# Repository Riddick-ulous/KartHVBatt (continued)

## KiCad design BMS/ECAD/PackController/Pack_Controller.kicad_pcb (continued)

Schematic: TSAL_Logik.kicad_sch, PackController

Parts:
C1001, C1002: 1uF 100V; C_0805_2012Metric
C1003, C1004, C1005, C1006, C1007, C1008: 100nC 16V; C_0603_1608Metric
D1001, D1002, D1003: BAT46; D_SOD-123
Q1001: FDN352AP; SOT-23
Q1002: BC846; SOT-23
R1001, R1002, R1003: 10kR 0603; R_0603_1608Metric_Pad0.98x0.95mm_HandSolder
R1004, R1005: 100kR; R_0603_1608Metric
R1006: 1kR; R_0603_1608Metric
U1001: SN74LVC2G02; VSSOP-8_2.3x2mm_P0.5mm
U1002: 74LVC86AD; SO-14_3.9x8.65mm_P1.27mm
U1003: 74LV08; SO-14_3.9x8.65mm_P1.27mm
U1004: 74LVC1G32Q; SOT-353_SC-70-5
U1005: SN74LVC1G74; VSSOP-8_2.3x2mm_P0.5mm
U1006: CD4072BPW; TSSOP-14_4.4x5mm_P0.65mm
U1007: SN74LVC2G17DCK; SOT-23-6
U1008: SN74LVC2G14DBV; SOT-23-6

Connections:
+3.3V: C1003.1, C1004.1, C1005.1, C1006.1, C1007.1, C1008.1, D1001.1 (K), R1005.2, U1001.8 (VCC), U1002.14 (VCC), U1003.14 (VCC), U1004.5 (VCC), U1005.4 (GND), U1006.14 (VDD), U1007.5 (V_{CC}), U1008.5 (V_{CC}); also elsewhere on the board
+BATT: Q1001.2 (S), R1001.2; also elsewhere on the board
/AIR/AIR_N_Actual: U1002.5, U1003.2, U1006.10; also elsewhere on the board
/AIR/AIR_N_Intended: U1002.4, U1002.9; also elsewhere on the board
/AIR/AIR_P_Actual: U1002.2, U1006.9; also elsewhere on the board
/AIR/AIR_P_Intended: U1002.1; also elsewhere on the board
/AIR/nAIR_Error: U1008.1 (1A); also elsewhere on the board
/HV_Measurement/nDANGER_V: U1003.1, U1008.3 (2A); also elsewhere on the board
/MCU/PCHRG_ACTUAL: U1002.10, U1004.2, U1006.11; also elsewhere on the board
/MCU/TSAL_GRN_ON: R1003.2, U1003.8; also elsewhere on the board
/Precharge/PCHRG_Intended: U1004.1; also elsewhere on the board
/TSAL_GRN: D1003.1 (K); also elsewhere on the board
/TSAL_Logik/AIR_Error: U1001.2, U1008.6 (1Y)
/TSAL_Logik/DANGER_V: U1006.12, U1008.4 (2Y)
/TSAL_Logik/TS_ON: U1001.6, U1006.13
GND: C1001.2, C1002.2, C1003.2, C1004.2, C1005.2, C1006.2, C1007.2, C1008.2, Q1002.2 (E), U1001.4 (GND), U1002.7 (GND), U1002.12, U1002.13, U1003.7 (GND), U1003.12, U1003.13, U1004.3 (GND), U1005.1 (CLK), U1005.2 (D), U1005.8 (VCC), U1006.7 (VSS), U1007.2 (GND), U1008.2 (GND); also elsewhere on the board
unnamed: C1002.1, D1001.2 (A), R1005.1, U1007.3 (2A)
unnamed: D1002.2 (A), R1004.1, U1001.7
unnamed: D1002.1 (K), R1006.1
unnamed: D1003.2 (A), Q1001.3 (D)
unnamed: Q1001.1 (G), R1002.2
unnamed: Q1002.1 (B), R1003.1
unnamed: Q1002.3 (C), R1001.1, R1002.1
unnamed: U1001.1, U1006.1
unnamed: U1001.3, U1003.9
unnamed: U1002.3, U1006.2
unnamed: U1002.6, U1006.3
unnamed: U1002.8, U1006.4
unnamed: U1003.3, U1003.4
unnamed: U1003.5, U1004.4
unnamed: U1003.6, U1006.5
unnamed: U1001.5, U1005.5 (Q)
unnamed: U1003.10, U1005.6 (nCLR), U1007.4 (2Y)
unnamed: U1005.7 (nPRE), U1007.6 (1Y)
unnamed: C1001.1, R1004.2, R1006.2, U1007.1 (1A)

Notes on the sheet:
RC filter delays error detection to filter out AIR operate-/release-times and other timing discrepancies that arise from hardware design.
ERROR = !(AIR_P_ACT == AIR_P_INT) or !(AIR_N_ACT == AIR_N_INT) or !(PCHRG_ACT == AIR_N_INT) or (!DANGER_V and AIR_N_ACT and (PCHRG_ACT or AIR_P_ACT)) or AIR_ERROR TS_ON = AIR_P_ACT or AIR_N_ACT or PCHRG_ACT or DANGER_V GREEN = !(TS_ON or ERROR_LATCH)
POR: Capacitor charges from 0V to 3.3V when power supply is applied. This triggers the clear function of the flip-flop. POR keeps nCLR active for approximately 50...95 ms nominal. Actual delay depends on Schmitt threshold and RC tolerances. GRN_ON-signal also ANDed with POR to only display green af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
base/gate-resistors: 12V/10kOhm 1.2mA 3.3V/10kOhm 0.33mA pullup: reset against eventual leakage of the NPN

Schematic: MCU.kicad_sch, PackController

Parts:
C201, C202, C203, C204, C206, C209, C210, C213, C214: 100nF 0603 6.3V; C_0603_1608Metric_Pad1.08x0.95mm_HandSolder
C205: 6 * 100nF 0603 6.3V; C_0603_1608Metric_Pad1.08x0.95mm_HandSolder
C207: 4.7uF 0805 6.3V; C_0805_2012Metric_Pad1.18x1.45mm_HandSolder
C208: 100nF 0603 16V; C_0603_1608Metric_Pad1.08x0.95mm_HandSolder
C211: 12pF 0603 6.3V; C_0603_1608Metric_Pad1.08x0.95mm_HandSolder
C212: 2 * 12pF 0603 6.3V; C_0603_1608Metric_Pad1.08x0.95mm_HandSolder
D201, D203, D204, D205, D206, D207, D209: BAT46; D_SOD-123
D202: Z 3.3V; D_SOD-323_HandSoldering; PartNr. MM3Z3V3T1G
Error201: LED Red; LED_0805_2012Metric_Pad1.15x1.40mm_HandSolder
Heart201: LED Blue; LED_0805_2012Metric_Pad1.15x1.40mm_HandSolder
JTAG201: JTAG/SWD; PinHeader_2x07_P1.27mm_Vertical
Q201: DMP4065S-7; SOT-23-3
Q202: BC846; SOT-23
R201, R215, R217, R218, R219: 10kR 0603; R_0603_1608Metric_Pad0.98x0.95mm_HandSolder
R202: 2.2k 0603; R_0603_1608Metric_Pad0.98x0.95mm_HandSolder
R203, R205, R206, R207, R208, R211, R213: 10kR; R_0603_1608Metric_Pad0.98x0.95mm_HandSolder
R204, R210, R212: 100R 0603; R_0603_1608Metric_Pad0.98x0.95mm_HandSolder
R209, R216: 20R 0603; R_0603_1608Metric_Pad0.98x0.95mm_HandSolder
R214: 220kR; R_0603_1608Metric_Pad0.98x0.95mm_HandSolder
U201: MCP130-270 ITT; SOT-23
U202: STWD100YNYWY; SOT-23-5
U203: SN74LVC1G74; VSSOP-8_2.3x2mm_P0.5mm
U204: STM32G483VET6; LQFP-100_14x14mm_P0.5mm
U205: 24LC256-I/SN; SOIC-8_5.3x5.3mm_P1.27mm
Y201: WE830055951; Oscillator_SMD_EuroQuartz_XO32-4Pin_3.2x2.5mm

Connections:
+3.3V: C201.1, C202.1, C203.1, C204.1, C205.1, C206.1, C207.1, C208.2, C209.2, C213.2, C214.2, JTAG201.3, R203.1, R206.1, R213.2, R217.2, R218.2, R219.2, U201.2 (VDD), U202.1 (VCC), U203.8 (VCC), U204.6 (VBAT), U204.24 (VDD), U204.36 (VREF+), U204.37 (VDDA), U204.49 (VDD), U204.64 (VDD), U204.75 (VDD), U204.100 (VDD), U205.8 (VCC); also elsewhere on the board
+BATT: R201.2; also elsewhere on the board
/AIR/AIR_N_Actual: U204.93 (PB6); also elsewhere on the board
/AIR/AIR_N_Intended: U204.92 (PB5); also elsewhere on the board
/AIR/AIR_N_Switch: U204.86 (PD4); also elsewhere on the board
/AIR/AIR_P_Actual: U204.89 (PD7); also elsewhere on the board
/AIR/AIR_P_Intended: U204.88 (PD6); also elsewhere on the board
/AIR/AIR_P_Switch: U204.85 (PD3); also elsewhere on the board
/AIR/SC_END: Q201.1 (D); also elsewhere on the board
/AIR/nAIR_Error: U204.94 (PB7); also elsewhere on the board
/Buzzer/Buzzer_CTRL: U204.27 (PA5); also elsewhere on the board
/CAN1/CAN_RX: R209.2; also elsewhere on the board
/CAN1/CAN_TX: U204.73 (PA12); also elsewhere on the board
/CAN2/CAN_RX: R216.2; also elsewhere on the board
/CAN2/CAN_TX: U204.52 (PB13); also elsewhere on the board
/DCDC_AIR/DCDC_AIR_ACTUAL: U204.16 (PC1); also elsewhere on the board
/DCDC_AIR/DCDC_AIR_SWITCH: U204.15 (PC0); also elsewhere on the board
/HV_Measurement/V_ACCU: U204.40 (PE9); also elsewhere on the board
/HV_Measurement/V_VEHI: U204.22 (PA2); also elsewhere on the board
/HV_Measurement/nDANGER_V: U204.26 (PA4); also elsewhere on the board
/HV_Measurement/nPRCHG_DONE: U204.83 (PD1); also elsewhere on the board
/HV_Measurement_DCDC/V_DCDC: U204.44 (PE13); also elsewhere on the board
/HumiditySensing/R_Leak_Sig1: U204.20 (PA0); also elsewhere on the board
/HumiditySensing/R_Leak_Sig2: U204.21 (PA1); also elsewhere on the board
/HumiditySensing/R_Leak_Supply1: U204.19 (PF2); also elsewhere on the board
/HumiditySensing/R_Leak_Supply2: U204.18 (PC3); also elsewhere on the board
/IMD_Monitoring/IMD_OK: U204.41 (PE10); also elsewhere on the board
/IMD_Monitoring/IMD_SC_Closed: U204.43 (PE12); also elsewhere on the board
/IMD_Monitoring/IMD_State: U204.42 (PE11); also elsewhere on the board
/IMD_Monitoring/SC_Out: Q201.3 (S), R205.1; also elsewhere on the board
/MCU/Boot0: R215.1, U204.95 (PB8)
/MCU/ERRQ: U204.61 (PD14); also elsewhere on the board
/MCU/ERRQ_Ioc_out: U204.57 (PD10); also elsewhere on the board
/MCU/ERRQ_ext: U204.59 (PD12); also elsewhere on the board
/MCU/ERRQ_ext_out: U204.58 (PD11); also elsewhere on the board
/MCU/ERRQ_res: U204.60 (PD13); also elsewhere on the board
/MCU/Error: Error201.2 (A), U204.3 (PE4)
/MCU/FAN_PWM: U204.2 (PE3); also elsewhere on the board
/MCU/Heart: Heart201.2 (A), U204.1 (PE2)
/MCU/NTC1_Sig: U204.28 (PA6); also elsewhere on the board
/MCU/NTC2_Sig: U204.39 (PE8); also elsewhere on the board
/MCU/NTC3_Sig: U204.45 (PE14); also elsewhere on the board
/MCU/NTC4_Sig: U204.53 (PB14); also elsewhere on the board
/MCU/NTC5_Sig: U204.30 (PC4); also elsewhere on the board
/MCU/PCHRG_ACTUAL: U204.84 (PD2); also elsewhere on the board
/MCU/PCHRG_SWITCH: U204.82 (PD0); also elsewhere on the board
/MCU/SCL1: R218.1, U204.70 (PA9), U205.6 (SCL)
/MCU/SDA1: R217.1, U204.69 (PA8), U205.5 (SDA)
/MCU/TSAL_GRN_ON: U204.9 (PC15); also elsewhere on the board
/MCU/UART_HS_RX: U204.31 (PC5); also elsewhere on the board
/MCU/UART_HS_TX: U204.97 (PE0); also elsewhere on the board
/MCU/UART_LS_RX: U204.25 (PA3); also elsewhere on the board
/MCU/UART_LS_TX: U204.87 (PD5); also elsewhere on the board
/MCU/WD_Beat: U202.4 (WDI), U204.98 (PE1)
/MCU/WP1: R219.1, U204.29 (PA7), U205.7 (WP)
/MCU/nSleep: U204.62 (PD15); also elsewhere on the board
Batt_Meas: C210.1, D202.1 (K), R201.1, R202.2, U204.33 (PB1)
GND: C201.2, C202.2, C203.2, C204.2, C205.2, C206.2, C207.2, C209.1, C210.2, C211.1, C212.1, C213.1, C214.1, JTAG201.5, JTAG201.7, JTAG201.11, Q202.2 (E), R202.1, R204.2, R210.2, R211.1, R212.1, R214.2, R215.2, U201.3 (VSS), U202.3 (!EN), U203.1 (CLK), U203.2 (D), U203.4 (GND), U204.23 (VSS), U204.35 (VSSA), U204.48 (VSS), U204.63 (VSS), U204.74 (VSS), U204.99 (VSS), U205.1 (A0), U205.2 (A1), U205.3 (A2), U205.4 (GND); also elsewhere on the board
JCLK/SWCLK: JTAG201.6, U204.77 (PA14)
JTDI/NC: JTAG201.10
JTDO/SWO: JTAG201.8, U204.90 (PB3)
JTMS/SWDIO: JTAG201.4, U204.76 (PA13)
Latch_SC: D205.1 (K), U204.65 (PC6)
unnamed: D202.2 (A), R204.1
unnamed: D205.2 (A), D206.2 (A), D207.2 (A), R213.1, U203.6 (nCLR)
unnamed: D209.2 (A), R208.2, U203.5 (Q)
unnamed: Error201.1 (K), R212.2
unnamed: Heart201.1 (K), R210.1
unnamed: Q201.2 (G), R205.2, R207.1
unnamed: Q202.1 (B), R208.1
unnamed: Q202.3 (C), R207.2
unnamed: C208.1, U202.2 (GND)
unnamed: R209.1, U204.72 (PA11)
unnamed: R216.1, U204.51 (PB12)
unnamed: C211.2, U204.12 (PF0), Y201.2
unnamed: C212.2, U204.13 (PF1), Y201.1
SC_Latched: D207.1 (K), R214.1, U204.67 (PC8)
SC_State: D209.1 (K), R211.2
T_VCP_RX: JTAG201.13
T_VCP_TX: JTAG201.14
nPOR: D201.1 (K), D204.1 (K), U201.1 (~RST), U203.7 (nPRE)
nPOR_State: D204.2 (A), R206.2, U204.66 (PC7)
nRES: D201.2 (A), D203.2 (A), JTAG201.12, R203.2, U204.14 (PG10), U204.91 (PB4)
nWDO: D203.1 (K), D206.1 (K), U202.5 (!WDO)

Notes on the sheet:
VBatt = 12V
Place close to VREF GND
SC latch / reset / watchdog logic: U201 MCP130 generates nPOR from +3.3V. nPOR is used only as power-on/brownout set signal for U203A. Power-up / brownout: nPOR = LOW -> U203A nPRE = LOW -> Q = HIGH -> Q202/Q201 enable SC_Out -> D201 also pulls nRES LOW and keeps MCU in reset After nPOR release: nP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

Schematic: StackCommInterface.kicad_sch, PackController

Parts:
C301, C302, C303: 100nF 16V; C_1206_3216Metric
C304: 330nF 50V; C_0805_2012Metric
C305, C306, C307, C308, C310, C311, C312: 2.2nC 100V; C_0603_1608Metric
C309: 2.2nC 1000V; C_0603_1608Metric
C313, C314, C315, C316: 220pC 100V; C_0603_1608Metric
R301: 5.1R; R_0603_1608Metric
R302, R303, R308, R309: 39R; R_0603_1608Metric
R304, R305, R306, R307, R312, R313: 1kR; R_0603_1608Metric
R310: 10kR; R_0603_1608Metric
R311: 1.5kR; R_0603_1608Metric
T301, T302: HM2106NL; Pulse_HM2106NL
U301: TLE9015 DQU; TQFP-48-1EP_7x7mm_P0.5mm_EP5x5mm

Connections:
+3.3V: C303.1, U301.30 (VIO); also elsewhere on the board
+BATT: R301.2; also elsewhere on the board
/MCU/ERRQ: R310.1, U301.33 (ERRQ); also elsewhere on the board
/MCU/ERRQ_Ioc_out: U301.21 (ERRQ_Ioc_out); also elsewhere on the board
/MCU/ERRQ_ext: U301.18 (ERRQ_ext); also elsewhere on the board
/MCU/ERRQ_ext_out: R311.2, U301.20 (ERRQ_ext_out); also elsewhere on the board
/MCU/ERRQ_res: U301.16 (ERRQ_res); also elsewhere on the board
/MCU/UART_HS_RX: R313.2, U301.29 (UART_HS); also elsewhere on the board
/MCU/UART_HS_TX: R313.1; also elsewhere on the board
/MCU/UART_LS_RX: R312.2, U301.28 (UART_LS); also elsewhere on the board
/MCU/UART_LS_TX: R312.1; also elsewhere on the board
/MCU/nSleep: U301.14 (nSleep); also elsewhere on the board
/StackCommInterface/IFH_H: R304.2, T301.1; also elsewhere on the board
/StackCommInterface/IFH_L: R304.1, T301.3; also elsewhere on the board
/StackCommInterface/IFL_H: R307.2, T302.1; also elsewhere on the board
/StackCommInterface/IFL_L: R307.1, T302.3; also elsewhere on the board
/StackCommInterface/VDDC: C304.1, R310.2, R311.1, U301.27 (VDDC)
GND: C301.2, C302.2, C303.2, C304.2, C313.2, C314.2, C315.2, C316.2, U301.22 (GND), U301.49 (EP); also elsewhere on the board
unnamed: C301.1, R301.1, U301.34 (VS), U301.35 (VS)
unnamed: C305.1, C306.2
unnamed: C305.2, R305.2, T301.6
unnamed: C306.1, C313.1, R302.1
unnamed: C307.1, C316.1, R303.1
unnamed: C307.2, C308.1
unnamed: C308.2, R306.2, T302.6
unnamed: C309.1, C310.2
unnamed: C309.2, R305.1, T301.4
unnamed: C310.1, C314.1, R308.1
unnamed: C311.1, C315.1, R309.1
unnamed: C311.2, C312.1
unnamed: C312.2, R306.1, T302.4
unnamed: R302.2, U301.25 (IFH_H)
unnamed: R308.2, U301.26 (IFH_L)
unnamed: R303.2, U301.24 (IFL_H)
unnamed: R309.2, U301.23 (IFL_L)
unnamed: C302.1, U301.31 (VregOut_VDDA)

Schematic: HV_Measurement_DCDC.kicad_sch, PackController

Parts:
C2002, C2006: 100nC 0603 50V; C_0603_1608Metric
C2003, C2015: 100nF 0603 100V; C_0603_1608Metric_Pad1.08x0.95mm_HandSolder
C2004: 100pC 0603 50V; C_0603_1608Metric
C2005, C2007: 10uF 0805 35V; C_0805_2012Metric
C2008: 100nC 0603 16V; C_0603_1608Metric
C2010: 1uC 0805 50V; C_0805_2012Metric
C2012: 1uC 0805 16V; C_0805_2012Metric
C2014: 1nC 0603 16V; C_0603_1608Metric
C2016: 1uF 0805 50V; C_0805_2012Metric
R2001: 270R 0805; R_0805_2012Metric_Pad1.20x1.40mm_HandSolder
R2004, R2005: 4.7MR 2512 3kV 0,1%; R_2512_6332Metric_Pad1.40x3.35mm_HandSolder
R2006: 26.1kR 2512 500V 0,1%; R_2512_6332Metric_Pad1.40x3.35mm_HandSolder
R2008: 1kR; R_0603_1608Metric_Pad0.98x0.95mm_HandSolder
U2002: TEA1-0505HI; Converter_DCDC_TRACO_TEA1-xxxxHI_THT
U2003: AMC0311R; AMC0311R Wide-body SOIC (DWV)
U2004: LP5907MFX-3.3; SOT-23-5

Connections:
+3.3V: C2006.1, U2003.6 (REFIN); also elsewhere on the board
+3.3V_DCDC: C2002.1, C2010.1, C2015.2, C2016.1, U2003.1 (VDD1), U2004.5 (OUT)
+5V: C2007.1, C2008.1, C2012.1, U2002.1 (+Vin), U2003.8 (VDD2); also elsewhere on the board
+5V_DCDC: C2003.2, C2005.1, R2001.2, U2002.7 (+Vout), U2004.1 (IN), U2004.3 (EN)
/DCDC_AIR/TS_P_DCDC: R2004.1; also elsewhere on the board
/HV_Measurement_DCDC/V_DCDC: C2014.1, R2008.1; also elsewhere on the board
/TS_N_ACCU: C2002.2, C2003.1, C2004.2, C2005.2, C2010.2, C2015.1, C2016.2, R2001.1, R2006.2, U2002.5 (-Vout), U2003.3 (SNSN), U2003.4 (GND1), U2004.2 (GND); also elsewhere on the board
GND: C2006.2, C2007.2, C2008.2, C2012.2, C2014.2, U2002.2 (-Vin), U2003.5 (GND2); also elsewhere on the board
unnamed: R2004.2, R2005.1
unnamed: C2004.1, R2005.2, R2006.1, U2003.2 (INP)
unnamed: R2008.2, U2003.7 (OUT)

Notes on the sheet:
HV ACCU VOLTAGE DIVIDER / 0...800 V R_TOP = R2004 + R2005 R_TOP = 4.7 MOhm + 4.7 MOhm = 9.4 MOhm R_SNS = R2006 = 26.1 kOhm k_DIV = R_SNS / (R_TOP + R_SNS) k_DIV = 26.1 k / (9.4 M + 26.1 k) k_DIV = 0.00276891 = 1 / 361.153 V_INP = V_HV * k_DIV V_INP @ 588 V = 1.628 V V_INP @ 800 V = 2.215 V AMC0311R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
AMC0311R TRANSFER FUNCTION V_REFIN = 3.3 V V_CLIP = 2.56 V G_AMC = V_REFIN / V_CLIP G_AMC = 3.3 V / 2.56 V G_AMC = 1.28906 V/V V_OUT = V_INP * G_AMC V_OUT = V_HV * k_DIV * G_AMC V_OUT = V_HV * 0.00356929 V_OUT = V_HV / 280.167 V_HV = V_OUT * 280.167 V_OUT @ 40 V = 0.143 V V_OUT @ 588 V = 2.099 V V_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
AMC INPUT LOW-PASS R_TH = R_TOP || R_SNS R_TH = 9.4 MOhm || 26.1 kOhm R_TH approx. 26.03 kOhm C_IN = C2004 = 100 pF tau_IN = R_TH * C_IN tau_IN approx. 2.60 us f_c,IN = 1 / (2 * pi * R_TH * C_IN) f_c,IN approx. 61.1 kHz t_10-90,IN approx. 2.2 * tau_IN t_10-90,IN approx. 5.7 us AMC OUTPUT / ADC LOW-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
4.4mm creepage per R for 2512 inch package

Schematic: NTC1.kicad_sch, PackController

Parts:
C1301: 100nF 0603 50V; C_0603_1608Metric_Pad1.08x0.95mm_HandSolder
D1301: DESD5V0S1BA-7; D_SOD-323
R1301: 10k 0.1% 25ppm/K; R_0603_1608Metric_Pad0.98x0.95mm_HandSolder
R1302: 10k; R_0603_1608Metric_Pad0.98x0.95mm_HandSolder

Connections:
+3.3V: R1301.1; also elsewhere on the board
/MCU/NTC1_Sig: C1301.2, R1302.1; also elsewhere on the board
/TempMeas/NTC1/NTC+: D1301.1 (A1), R1301.2, R1302.2; also elsewhere on the board
GND: C1301.1, D1301.2 (A2); also elsewhere on the board

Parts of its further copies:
C1401, C1501, C1502, C1503: 100nF 0603 50V; C_0603_1608Metric_Pad1.08x0.95mm_HandSolder
D1401, D1501, D1502, D1503: DESD5V0S1BA-7; D_SOD-323
R1401, R1501, R1503, R1505: 10k 0.1% 25ppm/K; R_0603_1608Metric_Pad0.98x0.95mm_HandSolder
R1402, R1502, R1504, R1506: 10k; R_0603_1608Metric_Pad0.98x0.95mm_HandSolder

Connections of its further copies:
+3.3V: R1401.1, R1501.1, R1503.1, R1505.1; also elsewhere on the board
/MCU/NTC2_Sig: C1401.2, R1402.1; also elsewhere on the board
/MCU/NTC3_Sig: C1501.2, R1502.1; also elsewhere on the board
/MCU/NTC4_Sig: C1502.2, R1504.1; also elsewhere on the board
/MCU/NTC5_Sig: C1503.2, R1506.1; also elsewhere on the board
/TempMeas/NTC2/NTC+: D1401.1 (A1), R1401.2, R1402.2; also elsewhere on the board
/TempMeas/NTC3/NTC+: D1501.1 (A1), R1501.2, R1502.2; also elsewhere on the board
/TempMeas/NTC4/NTC+: D1502.1 (A1), R1503.2, R1504.2; also elsewhere on the board
/TempMeas/NTC5/NTC+: D1503.1 (A1), R1505.2, R1506.2; also elsewhere on the board
GND: C1401.1, C1501.1, C1502.1, C1503.1, D1401.2 (A2), D1501.2 (A2), D1502.2 (A2), D1503.2 (A2); also elsewhere on the board

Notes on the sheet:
External NTC input: 10k NTC to GND, 10k 0.1% pullup to 3V3. ADC is ratiometric to 3V3. R_NTC = R_PULLUP * x / (1 - x) x = ADC_raw / ADC_max R58/C49 form ADC input filter: tau = 10k * 100nF = 1ms, fc ≈ 159Hz. Open NTC -> ADC near full scale. Short to GND -> ADC near 0.

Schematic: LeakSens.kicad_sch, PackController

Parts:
C1601: 1nF 0603 16V; C_0603_1608Metric_Pad1.08x0.95mm_HandSolder
R1601: R_Leak; R_0603_1608Metric_Pad0.98x0.95mm_HandSolder
R1602, R1605: 10kR 0603; R_0603_1608Metric_Pad0.98x0.95mm_HandSolder
R1603: 1MR 0603; R_0603_1608Metric_Pad0.98x0.95mm_HandSolder
R1604: 10MR 0603; R_0603_1608Metric_Pad0.98x0.95mm_HandSolder

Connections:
/HumiditySensing/LeakSens1/R_Leak_ElecIn: R1602.2; also elsewhere on the board
/HumiditySensing/LeakSens1/R_Leak_ElecOut: R1603.1, R1605.2; also elsewhere on the board
/HumiditySensing/R_Leak_Sig1: C1601.2, R1605.1; also elsewhere on the board
/HumiditySensing/R_Leak_Supply1: R1602.1; also elsewhere on the board
GND: C1601.1, R1603.2; also elsewhere on the board

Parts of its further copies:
C1701: 1nF 0603 16V; C_0603_1608Metric_Pad1.08x0.95mm_HandSolder
R1702, R1705: 10kR 0603; R_0603_1608Metric_Pad0.98x0.95mm_HandSolder
R1703: 1MR 0603; R_0603_1608Metric_Pad0.98x0.95mm_HandSolder

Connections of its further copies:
/HumiditySensing/LeakSens2/R_Leak_ElecIn: R1702.2; also elsewhere on the board
/HumiditySensing/LeakSens2/R_Leak_ElecOut: R1703.1, R1705.2; also elsewhere on the board
/HumiditySensing/R_Leak_Sig2: C1701.2, R1705.1; also elsewhere on the board
/HumiditySensing/R_Leak_Supply2: R1702.1; also elsewhere on the board
GND: C1701.1, R1703.2; also elsewhere on the board

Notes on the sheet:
Leakage sensor: Flex electrodes form R_LEAK. R_EOL = 10M is mounted on the flex sensor, parallel to the electrodes, for open-wire detection. R_SENSOR = R_LEAK || R_EOL Measurement: Pulse R_Leak_Supply HIGH, wait 10...50ms, sample ADC, then set supply LOW/Hi-Z. Suggested scan rate: 1Hz. ADC conversi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

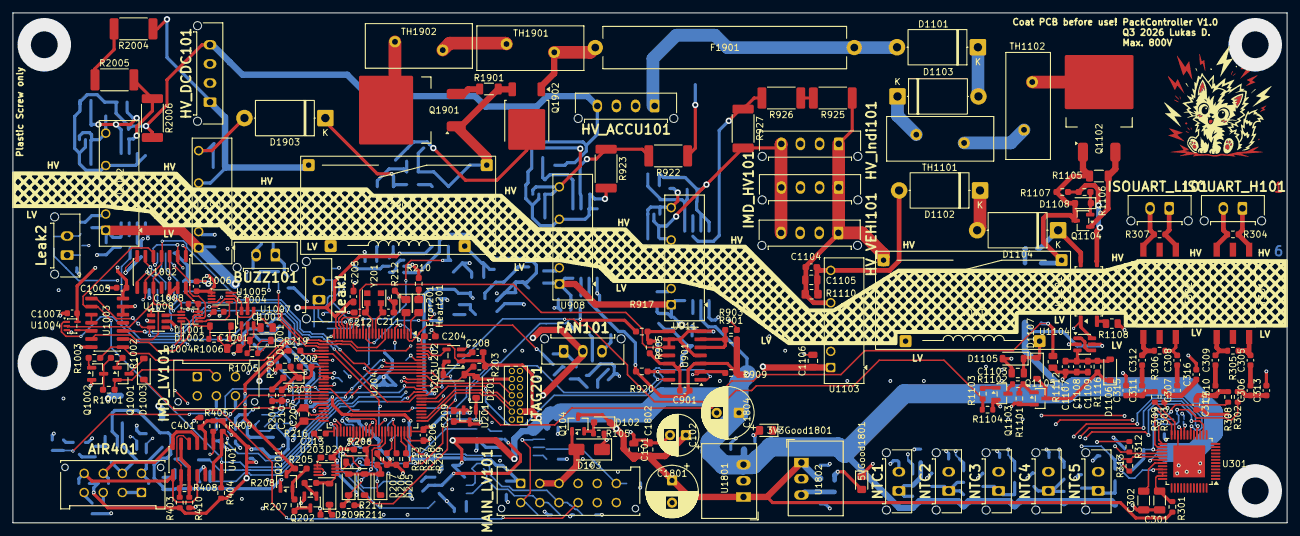
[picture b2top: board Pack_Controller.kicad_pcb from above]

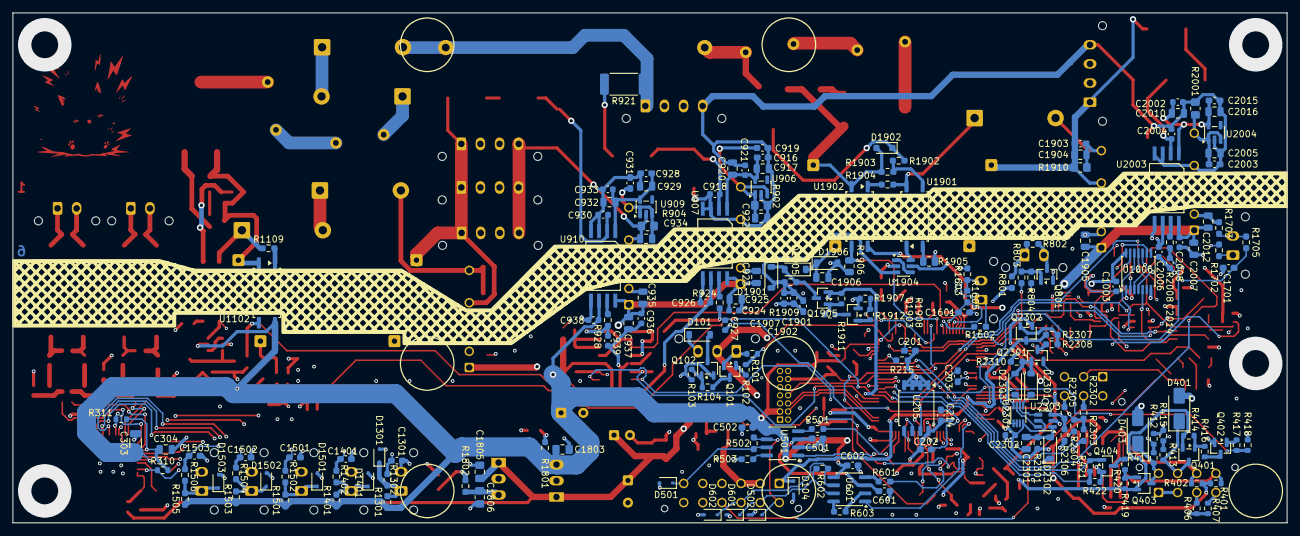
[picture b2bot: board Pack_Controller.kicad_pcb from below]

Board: 6 copper layers, 199.9 x 80.0 mm, 395 parts (192 on the bottom side), 243 nets.

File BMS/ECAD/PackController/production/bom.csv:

Designator,Footprint,Quantity,Value,LCSC Part #
"3V3GOOD1801, 5VGOOD1801",0805,2,LED Green,
AIR401,Molex_Micro-Fit_3.0_43045-0812_2x04_P3.00mm_Vertical,1,~,
"BUZZ101, LEAK2, NTC1, NTC2, NTC3, NTC4, NTC5",Molex_Micro-Fit_3.0_43650-0215_1x02_P3.00mm_Vertical,7,~,
"C1001, C1002",0603,2,1uF 16V,
"C1003, C1004, C1005, C1006, C1007, C1008, C2302",0603,7,100nC 16V,
C101,1206,1,10uF 1206 25V,
C102,CP_Radial_D6.3mm_P2.50mm,1,47uF 25V,
"C1103, C1906",0805,2,10uF 0805 25V,
"C1104, C1107, C1108, C1109, C1901, C1902, C1903, C1907, C2003, C2015, C916, C919, C928, C931",0603,14,100nF 0603 100V,
"C1105, C1106, C1904, C1905, C2005, C2007, C922, C923, C934, C935",0805,10,10uF 0805 50V,
"C1301, C1401, C1501, C1502, C1503",0603,5,100nF 0603 50V,
"C1601, C1701",0603,2,1nF 0603 16V,
C1801,CP_Radial_D8.0mm_P3.50mm,1,470uF 35V WE870025374007,
"C1802, C1803, C1805, C1806",0805,4,10uF 0805 35V,
C1804,CP_Radial_D8.0mm_P3.50mm,1,100uF 35V WE870025374007,
"C2002, C2006, C921, C926, C933, C938",0603,6,100nC 0603 50V,
"C2004, C918, C930",0603,3,100pC 0603 50V,
"C2008, C924, C936",0603,3,100nC 0603 16V,
"C201, C202, C203, C204, C206, C209, C210, C213, C214",0603,9,100nF 0603 6.3V,
"C2010, C920, C932",0805,3,1uC 0805 50V,
"C2012, C925, C937",0805,3,1uC 0805 16V,
"C2014, C927, C939",0603,3,1nC 0603 16V,
"C2016, C917, C929",0805,3,1uF 0805 50V,
C205,0603,1,6 * 100nF 0603 6.3V,
C207,0805,1,4.7uF 0805 6.3V,
"C208, C501, C502, C601, C602",0603,5,100nF 0603 16V,
C211,0603,1,12pF 0603 6.3V,
C212,0603,1,2 * 12pF 0603 6.3V,
C2301,0805,1,10uF 0805 16V,
"C301, C302, C303",1206,3,100nF 16V,
C304,1206,1,330nF 16V,
"C305, C306, C307, C308, C309, C310, C311, C312",1206,8,2.2nC 1000V,
"C313, C314, C315, C316",1206,4,220pC 1000V,
C401,0603,1,100nC 6V,
C901,0603,1,100n 0603 50V,
"D1001, D1002, D1003, D101, D1105, D1106, D1107, D1901, D1905, D1906, D201, D203, D204, D205, D206, D207, D209, D2301, D2302, D2303",D_SOD-123,20,BAT46,
D102,D_SOD-323_HandSoldering,1,Z 12V (MM3Z12VT1G),
D103,D_SMA,1,SMAJ15CA,
"D1101, D1102, D1103, D1104, D1903",D_DO-201AE_P12.70mm_Horizontal,5,BY2000,
"D1108, D1902",D_SOD-323_HandSoldering,2,MM3Z10VT1G (10V),
"D1301, D1401, D1501, D1502, D1503, D501, D502, D601, D602",D_SOD-323,9,DESD5V0S1BA-7,
D202,D_SOD-323_HandSoldering,1,Z 3.3V,
"D401, D403",D_SMA,2,B140-13-F,
ERROR201,0805,1,LED Red,
F1901,R_Axial_Power_L38.0mm_W6.4mm_P40.64mm,1,"2,5A 800V 0ADBP2500-RE",
FAN101,Molex_Micro-Fit_3.0_43650-0315_1x03_P3.00mm_Vertical,1,~,
HEART201,0805,1,LED Blue,
"HV_ACCU101, HV_DCDC101, HV_INDI101, HV_VEHI101, IMD_HV101",Molex_Micro-Fit_3.0_43650-0415_1x04_P3.00mm_Vertical,5,436500415,
IMD_LV101,Molex_Micro-Fit_3.0_43045-0612_2x03_P3.00mm_Vertical,1,~,
"ISOUART_H101, ISOUART_L101",Molex_Micro-Fit_3.0_43650-0215_1x02_P3.00mm_Vertical,2,436500227,
JTAG201,PinHeader_2x07_P1.27mm_Vertical,1,JTAG/SWD,
"K1101, K1901",Meder_KT_Relay,2,KT12-1A-40L-THT,
LEAK1,Molex_Micro-Fit_3.0_43650-0215_1x02_P3.00mm_Vertical,1,Conn_01x02,
MAIN_LV101,Molex_Micro-Fit_3.0_43045-1212_2x06_P3.00mm_Vertical,1,~,
Q1001,SOT-23,1,FDN352AP,
"Q1002, Q101, Q1103, Q1903, Q202, Q2301, Q402, Q404",SOT-23,8,BC846,
"Q102, Q104, Q1101, Q1904, Q201, Q2302, Q401, Q403",SOT-23-3,8,DMP4065S-7,
"Q1102, Q1901",TO-263HV,2,IXTA08N100D2HV,
Q1104,SOT-23-3,1,IRLML0100TR,
Q1902,TO-252-2,1,IPD95R750P7,
Q801,SOT-23,1,2N7002,
"R1001, R1002, R1003, R1602, R1605, R1702, R1705, R201, R215, R217, R218, R219, R804",0603,13,10kR 0603,
"R1004, R1005",0603,2,100kR,
"R1006, R102, R2008, R2310, R304, R305, R306, R307, R312, R313, R401, R402, R403, R406, R407, R408, R410, R417, R421, R924, R928",0603,21,1kR,
"R101, R103, R104, R105, R1101, R1102, R1104, R1907, R1911, R1912, R203, R205, R206, R207, R208, R211, R213, R2306, R2307, R2308, R310, R404, R405, R409, R412, R414, R415, R416, R418, R419, R420, R422, R909, R920",0603,34,10kR,
"R1103, R1908",0603,2,4k7R,
"R1105, R1901",1206,2,47R 0603,
"R1106, R1902, R204, R210, R212, R801",0603,6,100R 0603,
"R1107, R1116, R1903, R1909",0603,4,100kR 0603,
"R1108, R1905",0805,2,"330R 0805 0,25W",
"R1109, R1801, R1802, R1904, R503, R603, R803",0603,7,1kR 0603,
"R1110, R1910, R2001, R902, R904",0805,5,270R 0805,
"R1112, R1906",0805,2,"10kR 0805 0,25W",
"R1301, R1401, R1501, R1503, R1505",0603,5,10k 0.1% 25ppm/K,
"R1302, R1402, R1502, R1504, R1506",0603,5,10k,
"R1603, R1703",0603,2,1MR 0603,
"R2004, R2005, R921, R922, R925, R926",2512,6,"4.7MR 2512 3kV 0,1%",
"R2006, R923, R927",2512,3,"26.1kR 2512 500V 0,1%",
R202,0603,1,2.2k 0603,
"R209, R216, R501, R601",0603,4,20R 0603,
R214,0603,1,220kR,
R2301,0603,1,1.5MR,
"R2302, R2303, R2304",0603,3,See Note,
"R2305, R411, R413",0603,3,39kR,
R301,0603,1,5.1R,
"R302, R303, R308, R309",0603,4,39R,
R311,0603,1,1.5kR,
"R502, R602",0603,2,120R 0603,
R802,0603,1,2.2kR 0603,
R901,0603,1,68.1K 0.1%,
"R903, R910",0603,2,3.9k 0.1%,
R908,0603,1,"68,1K 0.1%",
"R915, R917",0603,2,100kR 0.1%,
"R918, R919",0603,2,909kR 0.1%,
"T301, T302",Pulse_HM2106NL,2,HM2106NL,
"TH1101, TH1102, TH1901, TH1902",RV_Disc_D16.5mm_W6.7mm_P7.5mm,4,PTCEL17R501TBE,
U1001,VSSOP-8_2.3x2mm_P0.5mm,1,SN74LVC2G02,
U1002,SO-14_3.9x8.65mm_P1.27mm,1,74LVC86AD,
U1003,SO-14_3.9x8.65mm_P1.27mm,1,74LV08,
U1004,SOT-353_SC-70-5,1,74LVC1G32Q,
"U1005, U203, U2301",VSSOP-8_2.3x2mm_P0.5mm,3,SN74LVC1G74,
U1006,TSSOP-14_4.4x5mm_P0.65mm,1,CD4072BPW,
"U1007, U2303",SOT-23-6,2,SN74LVC2G17DCK,
"U1008, U1104, U1904",SOT-23-6,3,SN74LVC2G14DBV,
"U1101, U1102, U1901, U1902",SOP-4_7.5x4.1mm_P2.54mm,4,TCLT1004,
"U1103, U1903, U2002, U908, U911",Converter_DCDC_TRACO_TEA1-xxxxHI_THT,5,TEA1-0505HI,
U1801,Converter_DCDC_RECOM_R-78E-0.5_THT,1,R-78E3.3-1.0,
U1802,Converter_DCDC_RECOM_R-78E-0.5_THT,1,R-78E5.0-1.0,
"U2003, U907, U910",AMC0311R Wide-body SOIC (DWV),3,AMC0311R,
"U2004, U906, U909",SOT-23-5,3,LP5907MFX-3.3,
U201,SOT-23,1,MCP130-270 ITT,
U202,SOT-23-5,1,STWD100YNYWY,
U204,LQFP-100_14x14mm_P0.5mm,1,STM32G483VET6,
U205,SOIC-8_5.3x5.3mm_P1.27mm,1,24LC256-I/SN,
U301,TQFP-48-1EP_7x7mm_P0.5mm_EP5x5mm,1,TLE9015 DQU,
"U401, U901",SOIC-14_3.9x8.7mm_P1.27mm,2,ADCMP393ARZ,
"U501, U601",SOIC-8_3.9x4.9mm_P1.27mm,2,MCP2562-E-SN,
Y201,Oscillator_SMD_EuroQuartz_XO32-4Pin_3.2x2.5mm,1,WE830055951,

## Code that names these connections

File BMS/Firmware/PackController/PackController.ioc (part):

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Mcu.Name=STM32G483VETx
Mcu.Package=LQFP100
Mcu.UserName=STM32G483VETx
PA0.GPIOParameters=GPIO_Label
PA0.GPIO_Label=R_Leak_sig1
PA0.Mode=IN1-Single-Ended
PA0.Signal=ADC1_IN1
PA1.GPIOParameters=GPIO_Label
PA1.GPIO_Label=R_Leak_sig2
PA1.Mode=IN2-Single-Ended
PA1.Signal=ADC2_IN2
PA11.Mode=FDCAN_Activate
PA11.Signal=FDCAN1_RX
PA12.Mode=FDCAN_Activate
PA12.Signal=FDCAN1_TX
PA13.Mode=JTAG_5_pins
PA13.Signal=SYS_JTMS-SWDIO
PA14.Mode=JTAG_5_pins
PA14.Signal=SYS_JTCK-SWCLK
PA15.Mode=JTAG_5_pins
PA15.Signal=SYS_JTDI
PA2.GPIOParameters=GPIO_Label
PA2.GPIO_Label=V_VEHI
PA2.Mode=IN3-Single-Ended
PA2.Signal=ADC1_IN3
PA3.Mode=Asynchronous
PA3.Signal=USART2_RX
PA4.GPIOParameters=GPIO_Label
PA4.GPIO_Label=nDANGER_V
PA4.Signal=GPIO_Input
PA5.GPIOParameters=GPIO_Label
PA5.GPIO_Label=BUZZ_CTRL
PA5.Signal=S_TIM2_CH1
PA6.GPIOParameters=GPIO_Label
PA6.GPIO_Label=NTC1_Sig
PA6.Mode=IN3-Single-Ended
PA6.Signal=ADC2_IN3
PA7.GPIOParameters=GPIO_Label
PA7.GPIO_Label=WP1
PA7.Signal=GPIO_Output
PA8.Mode=I2C
PA8.Signal=I2C2_SDA
PA9.Mode=I2C
PA9.Signal=I2C2_SCL
PB1.GPIOParameters=GPIO_Label
PB1.GPIO_Label=Batt_Meas
PB1.Mode=IN1-Single-Ended
PB1.Signal=ADC3_IN1
PB12.Mode=FDCAN_Activate
PB12.Signal=FDCAN2_RX
PB13.Mode=FDCAN_Activate
PB13.Signal=FDCAN2_TX
PB14.GPIOParameters=GPIO_Label
PB14.GPIO_Label=NTC4_Sig
PB14.Mode=IN5-Single-Ended
PB14.Signal=ADC1_IN5
PB3.Mode=JTAG_5_pins
PB3.Signal=SYS_JTDO-SWO
PB4.Mode=JTAG_5_pins
PB4.Signal=SYS_JTRST
PB5.GPIOParameters=GPIO_Label
PB5.GPIO_Label=AIR_N_Intended
PB5.Signal=GPIO_Input
PB6.GPIOParameters=GPIO_Label
PB6.GPIO_Label=AIR_N_Actual
PB6.Signal=GPIO_Input
PB7.GPIOParameters=GPIO_Label
PB7.GPIO_Label=AIR_Error
PB7.Signal=GPIO_Input
PC0.GPIOParameters=GPIO_Label
PC0.GPIO_Label=DCDC_AIR_SWITCH
PC0.Signal=GPIO_Output
PC1.GPIOParameters=GPIO_Label
PC1.GPIO_Label=DCDC_AIR_ACTUAL
PC1.Signal=GPIO_Input
PC15-OSC32_OUT.Signal=GPIO_Output
PC3.GPIOParameters=GPIO_Label
PC3.GPIO_Label=R_Leak2_Supply
PC3.Signal=GPIO_Output
PC4.Mode=IN5-Single-Ended
PC4.Signal=ADC2_IN5
PC5.Mode=Asynchronous
PC5.Signal=USART1_RX
PC6.GPIOParameters=GPIO_Label
PC6.GPIO_Label=Latch_SC
PC6.Signal=GPIO_Output
PC7.Signal=GPIO_Input
PC8.GPIOParameters=GPIO_Label
PC8.GPIO_Label=SC_Latched
PC8.Signal=GPIO_Input
PD0.GPIOParameters=GPIO_Label
PD0.GPIO_Label=PCHRG_SWITCH
PD0.Signal=GPIO_Output
PD1.GPIOParameters=GPIO_Label
PD1.GPIO_Label=nPRCHG_DONE
PD1.Signal=GPIO_Input
PD10.GPIOParameters=GPIO_Label
PD10.GPIO_Label=ERRQ_Ioc_out
PD10.Signal=GPIO_Input
PD11.GPIOParameters=GPIO_Label
PD11.GPIO_Label=ERRQ_ext_out
PD11.Signal=GPIO_Input
PD12.GPIOParameters=GPIO_Label
PD12.GPIO_Label=ERRQ_ext
PD12.Signal=GPIO_Output
PD13.GPIOParameters=GPIO_Label
PD13.GPIO_Label=ERRQ_res
PD13.Signal=GPIO_Output
PD14.GPIOParameters=GPIO_Label
PD14.GPIO_Label=ERRQ
PD14.Signal=GPIO_Input
PD15.GPIOParameters=GPIO_Label
PD15.GPIO_Label=nSleep
PD15.Signal=GPIO_Output
PD2.GPIOParameters=GPIO_Label
PD2.GPIO_Label=PCHRG_ACTUAL
PD2.Signal=GPIO_Input
PD3.GPIOParameters=GPIO_Label
PD3.GPIO_Label=AIR_P_Switch
PD3.Signal=GPIO_Output
PD4.GPIOParameters=GPIO_Label
PD4.GPIO_Label=AIR_N_Switch
PD4.Signal=GPIO_Output
PD5.Mode=Asynchronous
PD5.Signal=USART2_TX
PD6.GPIOParameters=GPIO_Label
PD6.GPIO_Label=AIR_P_Intended
PD6.Signal=GPIO_Input
PD7.GPIOParameters=GPIO_Label
PD7.GPIO_Label=AIR_P_Actual
PD7.Signal=GPIO_Input
PE0.Mode=Asynchronous
PE0.Signal=USART1_TX
PE1.GPIOParameters=GPIO_Label
PE1.GPIO_Label=WD_Beat
PE1.Signal=GPIO_Output
PE10.GPIOParameters=GPIO_Label
PE10.GPIO_Label=IMD_OK
PE10.Signal=GPIO_Input
PE11.GPIOParameters=GPIO_Label
PE11.GPIO_Label=IMD_State
PE11.Signal=GPIO_Input
PE12.GPIOParameters=GPIO_Label
PE12.GPIO_Label=IMD_SC_Closed
PE12.Signal=GPIO_Input
PE13.GPIOParameters=GPIO_Label
PE13.GPIO_Label=V_DCDC
PE13.Mode=IN3-Single-Ended
PE13.Signal=ADC3_IN3
PE14.GPIOParameters=GPIO_Label
PE14.GPIO_Label=NTC3_Sig
PE14.Mode=IN1-Single-Ended
PE14.Signal=ADC4_IN1
PE2.GPIOParameters=GPIO_Label
PE2.GPIO_Label=Heart_LED
PE2.Signal=GPIO_Output
PE3.GPIOParameters=GPIO_Label
PE3.GPIO_Label=FAN_PWM
PE3.Signal=S_TIM3_CH2
PE4.GPIOParameters=GPIO_Label
PE4.GPIO_Label=Error_LED
PE4.Signal=GPIO_Output
PE8.GPIOParameters=GPIO_Label
PE8.GPIO_Label=NTC2_Sig
PE8.Mode=IN6-Single-Ended
PE8.Signal=ADC5_IN6
PE9.GPIOParameters=GPIO_Label
PE9.GPIO_Label=V_ACCU
PE9.Mode=IN2-Single-Ended
PE9.Signal=ADC3_IN2
PF0-OSC_IN.Mode=HSE-External-Oscillator
PF0-OSC_IN.Signal=RCC_OSC_IN
PF1-OSC_OUT.Mode=HSE-External-Oscillator
PF1-OSC_OUT.Signal=RCC_OSC_OUT
PF2.GPIOParameters=GPIO_Label
PF2.GPIO_Label=R_Leak1_Supply
PF2.Signal=GPIO_Output
RCC.HSE_VALUE=8000000
RCC.SYSCLKFreq_VALUE=16000000
board=custom

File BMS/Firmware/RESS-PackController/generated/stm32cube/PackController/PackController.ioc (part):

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Mcu.Name=STM32G483VETx
Mcu.Package=LQFP100
Mcu.UserName=STM32G483VETx
PA0.GPIOParameters=GPIO_Label
PA0.GPIO_Label=RLeak1
PA0.Mode=IN1-Single-Ended
PA0.Signal=ADC1_IN1
PA1.GPIOParameters=GPIO_Label
PA1.GPIO_Label=RLeak2
PA1.Mode=IN2-Single-Ended
PA1.Signal=ADC2_IN2
PA11.Mode=FDCAN_Activate
PA11.Signal=FDCAN1_RX
PA12.Mode=FDCAN_Activate
PA12.Signal=FDCAN1_TX
PA13.Mode=JTAG_5_pins
PA13.Signal=SYS_JTMS-SWDIO
PA14.Mode=JTAG_5_pins
PA14.Signal=SYS_JTCK-SWCLK
PA15.Mode=JTAG_5_pins
PA15.Signal=SYS_JTDI
PA2.GPIOParameters=GPIO_Label
PA2.GPIO_Label=VVEHI
PA2.Mode=IN3-Single-Ended
PA2.Signal=ADC1_IN3
PA3.Mode=Asynchronous
PA3.Signal=USART2_RX
PA4.GPIOParameters=GPIO_Label
PA4.GPIO_Label=nDangerV
PA4.Signal=GPIO_Input
PA5.GPIOParameters=GPIO_Label
PA5.GPIO_Label=BuzzerPWM
PA5.Signal=S_TIM2_CH1
PA6.GPIOParameters=GPIO_Label
PA6.GPIO_Label=TNTC1
PA6.Mode=IN3-Single-Ended
PA6.Signal=ADC2_IN3
PA7.GPIOParameters=PinState,GPIO_Label
PA7.GPIO_Label=WP
PA7.PinState=GPIO_PIN_SET
PA7.Signal=GPIO_Output
PA8.Mode=I2C
PA8.Signal=I2C2_SDA
PA9.Mode=I2C
PA9.Signal=I2C2_SCL
PB1.GPIOParameters=GPIO_Label
PB1.GPIO_Label=VBatt
PB1.Mode=IN1-Single-Ended
PB1.Signal=ADC3_IN1
PB12.Mode=FDCAN_Activate
PB12.Signal=FDCAN2_RX
PB13.Mode=FDCAN_Activate
PB13.Signal=FDCAN2_TX
PB14.GPIOParameters=GPIO_Label
PB14.GPIO_Label=TNTC4
PB14.Mode=IN5-Single-Ended
PB14.Signal=ADC1_IN5
PB3.Mode=JTAG_5_pins
PB3.Signal=SYS_JTDO-SWO
PB4.Mode=JTAG_5_pins
PB4.Signal=SYS_JTRST
PB5.GPIOParameters=GPIO_Label
PB5.GPIO_Label=AIR_N_Intended
PB5.Signal=GPIO_Input
PB6.GPIOParameters=GPIO_Label
PB6.GPIO_Label=AIR_N_Actual
PB6.Signal=GPIO_Input
PB7.GPIOParameters=GPIO_Label
PB7.GPIO_Label=nAIR_Error
PB7.Signal=GPIO_Input
PC0.GPIOParameters=GPIO_Label
PC0.GPIO_Label=DCDC_AIR_SWITCH
PC0.Signal=GPIO_Output
PC1.GPIOParameters=GPIO_Label
PC1.GPIO_Label=DCDC_AIR_ACTUAL
PC1.Signal=GPIO_Input
PC15-OSC32_OUT.GPIOParameters=GPIO_Label
PC15-OSC32_OUT.GPIO_Label=TSAL_GRN_ON
PC15-OSC32_OUT.Signal=GPIO_Input
PC3.GPIOParameters=GPIO_Label
PC3.GPIO_Label=RLeak2Supply
PC3.Signal=GPIO_Output
PC4.GPIOParameters=GPIO_Label
PC4.GPIO_Label=TNTC5
PC4.Mode=IN5-Single-Ended
PC4.Signal=ADC2_IN5
PC5.Mode=Asynchronous
PC5.Signal=USART1_RX
PC6.GPIOParameters=GPIO_Label
PC6.GPIO_Label=LatchSC
PC6.Signal=GPIO_Output
PC7.GPIOParameters=GPIO_Label
PC7.GPIO_Label=nPOR_State
PC7.Signal=GPIO_Input
PC8.GPIOParameters=GPIO_Label
PC8.GPIO_Label=SC_Latched
PC8.Signal=GPIO_Input
PD0.GPIOParameters=GPIO_Label
PD0.GPIO_Label=PCHRG_SWITCH
PD0.Signal=GPIO_Output
PD1.GPIOParameters=GPIO_Label
PD1.GPIO_Label=nPRCHG_DONE
PD1.Signal=GPIO_Input
PD10.GPIOParameters=GPIO_Label
PD10.GPIO_Label=ERR_loc_out
PD10.Signal=GPIO_Input
PD11.GPIOParameters=GPIO_Label
PD11.GPIO_Label=ERR_ext_out
PD11.Signal=GPIO_Input
PD12.GPIOParameters=PinState,GPIO_Label
PD12.GPIO_Label=ERRQ_ext
PD12.PinState=GPIO_PIN_SET
PD12.Signal=GPIO_Output
PD13.GPIOParameters=PinState,GPIO_Label
PD13.GPIO_Label=ERRQ_res
PD13.PinState=GPIO_PIN_SET
PD13.Signal=GPIO_Output
PD14.GPIOParameters=GPIO_Label
PD14.GPIO_Label=ERRQ
PD14.Signal=GPIO_Input
PD15.GPIOParameters=PinState,GPIO_Label
PD15.GPIO_Label=nSleep
PD15.PinState=GPIO_PIN_SET
PD15.Signal=GPIO_Output
PD2.GPIOParameters=GPIO_Label
PD2.GPIO_Label=PCHRG_ACTUAL
PD2.Signal=GPIO_Input
PD3.GPIOParameters=GPIO_Label
PD3.GPIO_Label=AIR_P_Switch
PD3.Signal=GPIO_Output
PD4.GPIOParameters=GPIO_Label
PD4.GPIO_Label=AIR_N_Switch
PD4.Signal=GPIO_Output
PD5.Mode=Asynchronous
PD5.Signal=USART2_TX
PD6.GPIOParameters=GPIO_Label
PD6.GPIO_Label=AIR_P_Intended
PD6.Signal=GPIO_Input
PD7.GPIOParameters=GPIO_Label
PD7.GPIO_Label=AIR_P_Actual
PD7.Signal=GPIO_Input
PE0.Mode=Asynchronous
PE0.Signal=USART1_TX
PE1.GPIOParameters=GPIO_Label
PE1.GPIO_Label=WDBeat
PE1.Signal=GPIO_Output
PE10.GPIOParameters=GPIO_Label
PE10.GPIO_Label=IMDOK
PE10.Signal=GPIO_Input
PE11.GPIOParameters=GPIO_Label
PE11.GPIO_Label=IMD_State
PE11.Signal=S_TIM1_CH2
PE12.GPIOParameters=GPIO_Label
PE12.GPIO_Label=IMDSCClosed
PE12.Signal=GPIO_Input
PE13.GPIOParameters=GPIO_Label
PE13.GPIO_Label=VDCDC
PE13.Mode=IN3-Single-Ended
PE13.Signal=ADC3_IN3
PE14.GPIOParameters=GPIO_Label
PE14.GPIO_Label=TNTC3
PE14.Mode=IN1-Single-Ended
PE14.Signal=ADC4_IN1
PE2.GPIOParameters=GPIO_Label
PE2.GPIO_Label=Heartbeat
PE2.Signal=GPIO_Output
PE3.GPIOParameters=GPIO_Label
PE3.GPIO_Label=FANPWM
PE3.Signal=S_TIM3_CH2
PE4.GPIOParameters=GPIO_Label
PE4.GPIO_Label=ErrorLED
PE4.Signal=GPIO_Output
PE8.GPIOParameters=GPIO_Label
PE8.GPIO_Label=TNTC2
PE8.Mode=IN6-Single-Ended
PE8.Signal=ADC5_IN6
PE9.GPIOParameters=GPIO_Label
PE9.GPIO_Label=VACCU
PE9.Mode=IN2-Single-Ended
PE9.Signal=ADC3_IN2
PF0-OSC_IN.Mode=HSE-External-Oscillator
PF0-OSC_IN.Signal=RCC_OSC_IN
PF1-OSC_OUT.Mode=HSE-External-Oscillator
PF1-OSC_OUT.Signal=RCC_OSC_OUT
PF2.GPIOParameters=GPIO_Label
PF2.GPIO_Label=RLeak1Supply
PF2.Signal=GPIO_Output
RCC.HSE_VALUE=16000000
RCC.SYSCLKFreq_VALUE=160000000
RCC.SYSCLKSource=RCC_SYSCLKSOURCE_PLLCLK
board=custom

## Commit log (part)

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2026-02-28 docs stuff
2026-03-01 started stack controller design
2026-03-03 finish V09 of stack controller and HV indicator
2026-03-03 did AIR monitoring circuit and started SDC CTRL / logik
2026-03-07 IMD control circuit
2026-03-29 add several subcomponent starts
2026-03-29 DCDC converter 50%
2026-03-29 DCDC Schematic 80%
2026-05-23 architechture doku
2026-06-27 started layout BMS slave
2026-06-28 stack controller design close to finished
    look into mounting option
2026-06-28 pack controller close to finished and startet pack controller
2026-06-30 finished schemativ of precharge
